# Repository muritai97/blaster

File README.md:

# blaster
4+5*3+2+1 split keyboard (WIP)
layout mockup - optional encoder in place of left-most thumbcluster

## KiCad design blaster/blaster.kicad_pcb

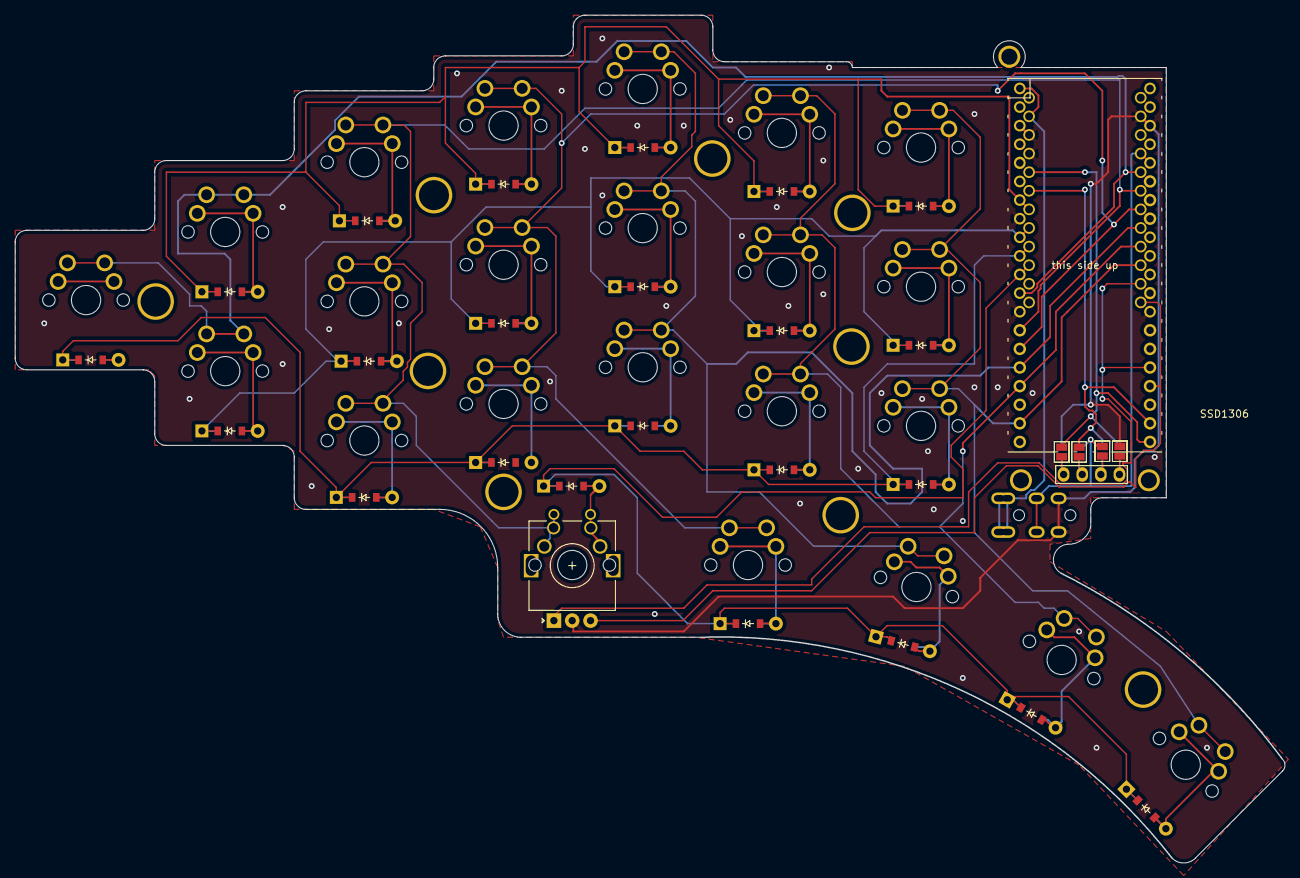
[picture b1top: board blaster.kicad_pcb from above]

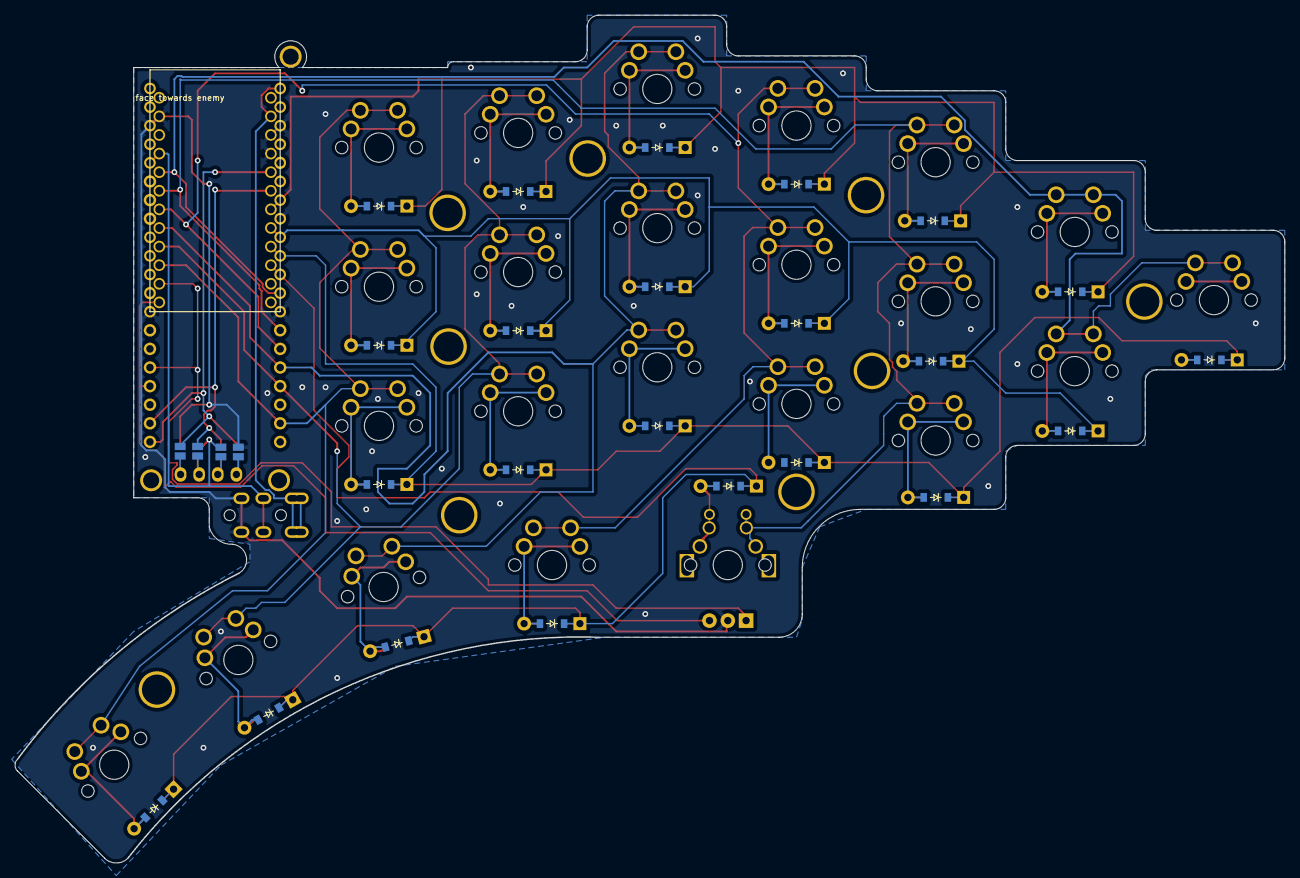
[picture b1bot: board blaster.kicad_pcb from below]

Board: 2 copper layers, 173.3 x 115.7 mm, 59 parts (2 on the bottom side), 39 nets.

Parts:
 : SolderJumper-2_P1.3mm_Open_Pad1.0x1.5mm
 #2: RotaryEncoder_Alps_EC11E-Switch_Vertical_H20mm
 #3,  #4,  #5,  #6,  #7,  #8,  #9: SolderJumper-2_P1.3mm_Open_Pad1.0x1.5mm
D1, D2, D3, D4, D5, D6, D7, D8, D9, D10, D11, D12, D13, D14, D15, D16, D17, D18, D19, D20, D21, D22, D23: ComboDiode
MCU1: this side down; ProMicro
S24, S25, S26, S27, S28, S29, S30, S31, S32, S33, S34, S35, S36, S37, S38, S39, S40, S41, S42, S43, S44, S45, S46: MX
SSD1306: 128x64OLED
TRRS1: TRRS-PJ-320A-dual
this side up: RPi_Pico_SMD_TH

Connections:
Data: MCU1.14, TRRS1.1, TRRS1.2, this side up.1
GND: #2.C, #7.1, #9.1, MCU1.2, MCU1.15, MCU1.16, TRRS1.4, this side up.3, this side up.8, this side up.13, this side up.28, this side up.38
SCL: #5.1, #6.1, MCU1.18, this side up.22
SDA: #3.1, #8.1, MCU1.17, this side up.21
VCC: .1, #4.1, MCU1.4, TRRS1.3, this side up.36
col0: MCU1.5, S24.1, S25.1, S26.1, this side up.12
col1: #2.S2, MCU1.6, S27.1, S28.1, S29.1, S42.1, S42.2, this side up.14
col2: MCU1.7, S31.1, S43.1, this side up.15
col3: MCU1.8, S33.1, S34.1, S35.1, S44.1, this side up.16
col4: MCU1.9, S36.1, S37.1, S38.1, S45.1, this side up.17
col5: MCU1.10, S39.1, S40.1, S41.1, S46.1, this side up.19
enc+: #2.A, MCU1.11, this side up.25
enc-: #2.B, MCU1.12, this side up.24
far_thumb: D23.2, S46.2
home_thumb: D22.2, S45.2
index_bottom: D13.2, S36.2
index_home: D14.2, S37.2
index_top: D15.2, S38.2
inner_bottom: D16.2, S39.2
inner_home: D17.2, S40.2
inner_top: D18.2, S41.2
middle_bottom: D10.2, S33.2
middle_home: D11.2, S34.2
middle_top: D12.2, S35.2
near1_thumb: D20.2, S43.2
near2_thumb: D21.2, S44.2
pinky_bottom: D4.2, S27.2
pinky_home: D5.2, S28.2
pinky_top: D6.2, S29.2
pinkycluster1_home: D1.2, S24.2
pinkycluster_home: D2.2, S25.2
pinkycluster_top: D3.2, S26.2
ring_bottom: D7.2, S30.2
ring_home: D8.2, S31.2
ring_top: D9.2, S32.2
row0: D3.1, D6.1, D9.1, D12.1, D15.1, D18.1, MCU1.19, this side up.e
row1: D2.1, D5.1, D8.1, D11.1, D14.1, D17.1, MCU1.20, this side up.9
row2: D1.1, D4.1, D7.1, D10.1, D13.1, D16.1, MCU1.21, this side up.10
row3: #2.S1, D19.1, D19.2, D23.1, MCU1.22, S42.1, S42.2, this side up.11

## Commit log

2023-04-21 base upload
